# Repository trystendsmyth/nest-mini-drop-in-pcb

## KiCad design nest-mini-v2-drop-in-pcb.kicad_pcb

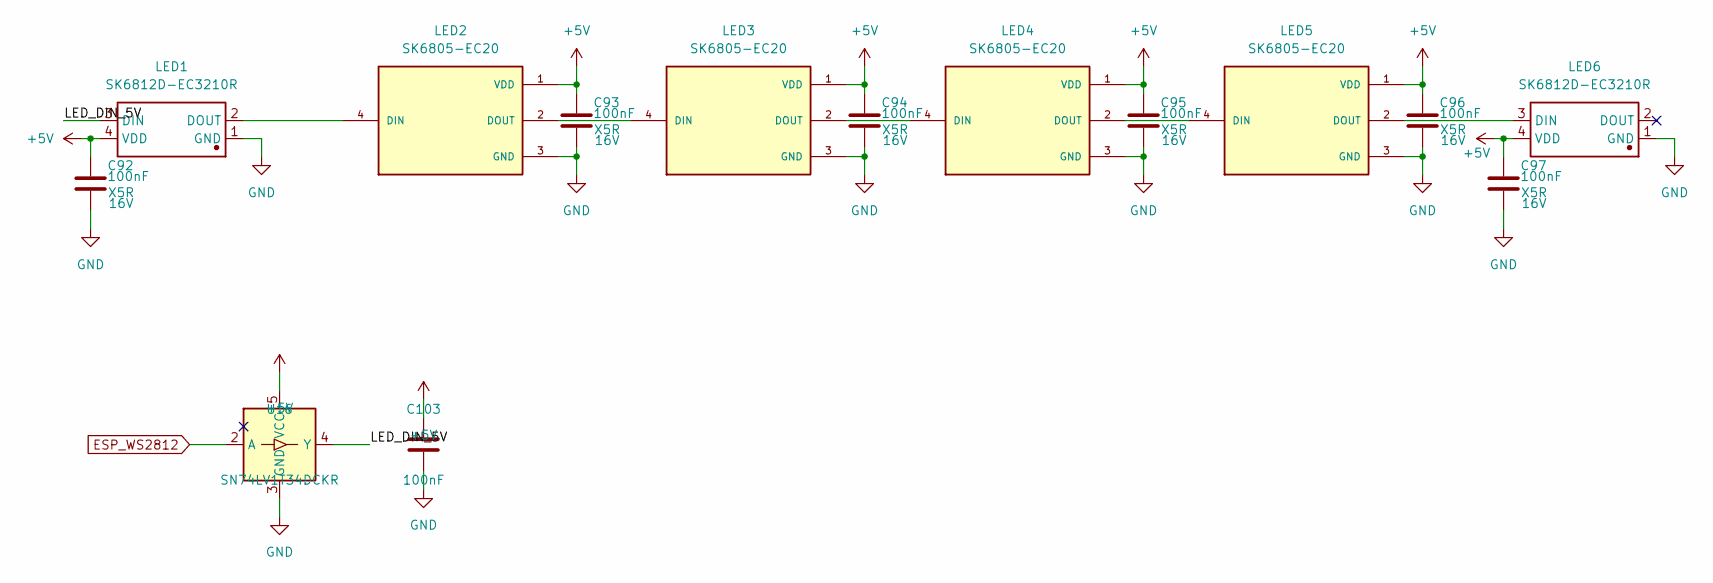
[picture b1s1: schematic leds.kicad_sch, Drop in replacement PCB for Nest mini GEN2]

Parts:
C92, C93, C94, C95, C96, C97: 100nF; C_0402_1005Metric; Voltage 16V; LCSC Part # C1525
C103: 100nF; C_0402_1005Metric; Manufacturer Part CL05B104KO5NNNC; LCSC Part # C1525
LED1, LED6: SK6812D-EC3210R; LED-SMD_4P_SK6812D-EC3210R; Manufacturer Part SK6812D-EC3210R; LCSC Part # C2890041
LED2, LED3, LED4, LED5: SK6805-EC20; Manufacturer Part SK6805-EC20; LCSC Part # C2890036
U16: SN74LV1T34DCKR; SOT-353_SC-70-5; MPN SN74LV1T34DCKR; LCSC Part # C78541

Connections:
+5V: C92.1, C93.1, C94.1, C95.1, C96.1, C97.1, C103.1, LED1.4 (VDD), LED2.1 (VDD), LED3.1 (VDD), LED4.1 (VDD), LED5.1 (VDD), LED6.4 (VDD), U16.5 (VCC); also elsewhere on the board
/LEDs/LED_DIN_5V: LED1.3 (DIN), U16.4 (Y)
ESP_WS2812: U16.2 (A); also elsewhere on the board
GND: C92.2, C93.2, C94.2, C95.2, C96.2, C97.2, C103.2, LED1.1 (GND), LED2.3 (GND), LED3.3 (GND), LED4.3 (GND), LED5.3 (GND), LED6.1 (GND), U16.3 (GND); also elsewhere on the board
unnamed: LED1.2 (DOUT), LED2.4 (DIN)
unnamed: LED2.2 (DOUT), LED3.4 (DIN)
unnamed: LED3.2 (DOUT), LED4.4 (DIN)
unnamed: LED4.2 (DOUT), LED5.4 (DIN)
unnamed: LED5.2 (DOUT), LED6.3 (DIN)

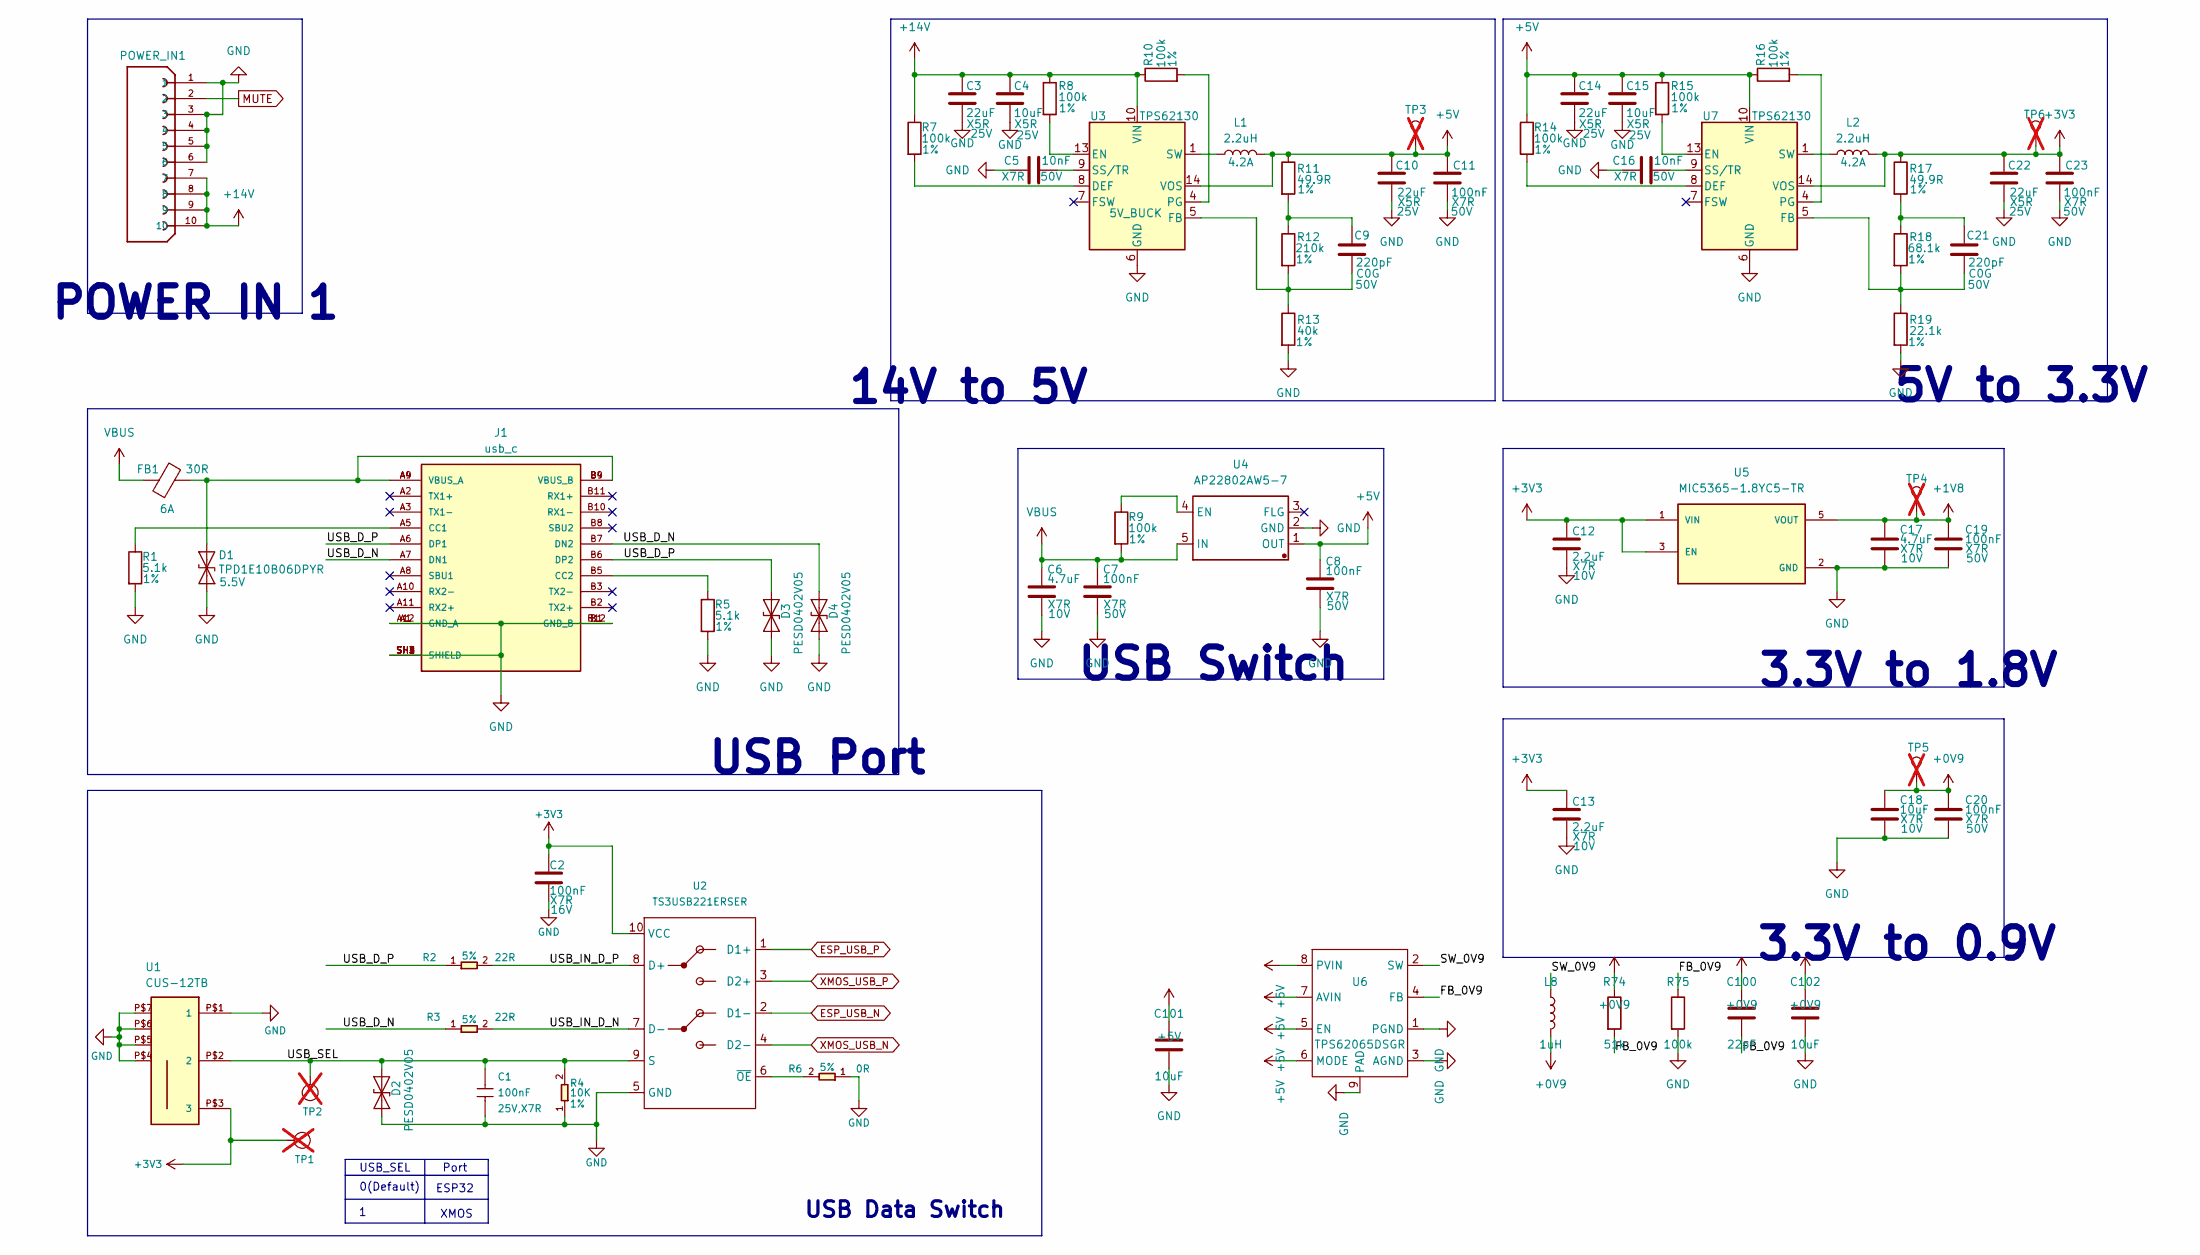
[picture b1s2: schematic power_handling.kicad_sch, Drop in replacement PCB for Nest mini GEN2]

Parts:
C1: 100nF; C_0402_1005Metric; Voltage Rating 25V,X7R; MPN CC0402KRX7R8BB104
C2: 100nF; C_0402_1005Metric; Voltage 16V; Manufacturer Part CL05B104KO5NNNC; LCSC Part # C1525
C3, C10, C14, C22: 22uF; C_0805_2012Metric; Voltage 25V; Manufacturer Part CL21A226MAQNNNE; LCSC Part # C45783
C4, C15: 10uF; C_0805_2012Metric; Voltage 25V; Manufacturer Part CL21A106KAYNNNE; LCSC Part # C15850
C5, C16: 10nF; C_0402_1005Metric; Voltage 50V; Manufacturer Part CL05B103KB5NNNC; LCSC Part # C15195
C6, C17: 4.7uF; C_0603_1608Metric; Voltage 10V; Manufacturer Part GRM188Z71A475KE15D; LCSC Part # C913474
C7, C8: 100nF; C_0603_1608Metric; Voltage 50V; Manufacturer Part CC0603KRX7R9BB104; LCSC Part # C14663
C9, C21: 220pF; C_0603_1608Metric; Voltage 50V; Manufacturer Part 0603CG221J500NT; LCSC Part # C156398
C11, C19, C20, C23: 100nF; C_0805_2012Metric; Voltage 50V; Manufacturer Part CC0805KRX7R9BB104; LCSC Part # C49678
C12, C13: 2.2uF; C_0603_1608Metric; Voltage 10V; Manufacturer Part GRM188R71A225KE15D; LCSC Part # C86018
C18, C101, C102: 10uF; C_0603_1608Metric; Voltage 10V; Manufacturer Part CL10A106KP8NNNC; LCSC Part # C19702
C100: 22pF; C_0402_1005Metric; Manufacturer Part CC0402JRNPO9BN220; LCSC Part # C106203
D1: TPD1E10B06DPYR; TPD1E05U06DPYR; Voltage 5.5V; Manufacturer Part TPD1E10B06DPYR; LCSC Part # C48260
D2, D4: PESD0402V05; D_0402_1005Metric; Manufacturer Part PESD0402V05; LCSC Part # C19626254
D3: PESD0402V05; D_0402_1005Metric; Part C19626254; LCSC Part # C19626254
FB1: 30R; R_0603_1608Metric; Part number BLM18PG300SN1D; LCSC Part # C17305
J1: usb_c; USB-C-SMD_TYPE-C-USB-18; Manufacturer Part 1054500101; LCSC Part # C134092
L1, L2: 2.2uH; L_Cenker_CKCS4020; Manufacturer Part SRP4020TA-2R2M; LCSC Part # C719179
L8: 1uH; L_Murata_DFE201610P; Manufacturer Part DFE201610E-1R0M=P2; LCSC Part # C161082
POWER_IN1: FH34SRJ-10S-0.5SH_50_; HRS_FH34SRJ-10S-0.5SH_50_; Manufacturer Part FH34SRJ-10S-0.5SH(50); LCSC Part # C324723
R1, R5: 5.1k; R_0402_1005Metric; Tolerance 1%; Manufacturer Part 0402WGF5101TCE; LCSC Part # C25905
R2, R3: 22R; R_0402_1005Metric; Tolerance 5%; MPN RC0402JR-0722RL
R4: 10K; R_0402_1005Metric; Tolerance 1%; MPN RC0402FR-0710KL
R6: 0R; R_0402_1005Metric; Tolerance 5%; MPN RC0402JR-070RL
R7, R8, R9, R10, R14, R15, R16: 100k; R_0402_1005Metric; Tolerance 1%; Manufacturer Part 0402WGJ0104TCE; LCSC Part # C25530
R11, R17: 49.9R; R_0603_1608Metric; Tolerance 1%; Manufacturer Part 0603WAF499JT5E; LCSC Part # C23185
R12: 210k; R_0603_1608Metric; Tolerance 1%; Manufacturer Part 0603WAF2103T5E; LCSC Part # C22952
R13: 40k; R_0603_1608Metric; Tolerance 1%; Manufacturer Part SCR0603F40K; LCSC Part # C3016445
R18: 68.1k; R_0603_1608Metric; Tolerance 1%; Manufacturer Part 0603WAF6812T5E; LCSC Part # C25976
R19: 22.1k; R_0603_1608Metric; Tolerance 1%; Manufacturer Part 0603WAF2212T5E; LCSC Part # C25961
R74: 51k; R_0402_1005Metric; Manufacturer Part RC0402FR-0751KL; LCSC Part # C107229
R75: 100k; R_0402_1005Metric; Manufacturer Part RC0402FR-07100KL; LCSC Part # C60491
TP1: Test Point; TestPoint_Pad_D1.0mm; not fitted
TP2: Test Point; TestPoint_Pad_D1.0mm; Part Type Test Point; not fitted
TP3, TP4, TP5, TP6: TestPoint; TestPoint_Pad_D1.0mm; not fitted
U1: CUS-12TB; CUS-12B
U2: TS3USB221ERSER; MPN TS3USB221ERSER; LCSC Part # C129313
U3, U7: TPS62130; VQFN-16-1EP_3x3mm_P0.5mm_EP1.68x1.68mm_ThermalVias; Manufacturer Part TPS62130ARGTR; LCSC Part # C337502
U4: AP22802AW5-7; SOT-23-5; Manufacturer Part AP22802AW5-7; LCSC Part # C211404
U5: MIC5365-1.8YC5-TR; SOT65P210X110-5N; PARTREV 3.1 - July 16, 2013; LCSC Part # C626087
U6: TPS62065DSGR; Texas_DSG0008A_WSON-8-1EP_2x2mm_P0.5mm_EP0.9x1.6mm; MPN TPS62065DSGR; LCSC Part # C398352

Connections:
+0V9: C18.1, C20.1, C100.1, C102.1, L8.2, R74.1, TP5.1; also elsewhere on the board
+1V8: C17.1, C19.1, TP4.1, U5.5 (VOUT); also elsewhere on the board
+3V3: C2.1, C12.1, C13.1, C22.1, C23.1, L2.2, R17.1, TP1.1 (T), TP6.1, U1.P$3 (3), U2.10 (VCC), U5.1 (VIN), U5.3 (EN), U7.14 (VOS); also elsewhere on the board
+5V: C8.1, C10.1, C11.1, C14.1, C15.1, C101.1, L1.2, R11.1, R14.1, R15.1, R16.1, TP3.1, U3.14 (VOS), U4.1 (OUT), U6.5 (EN), U6.6 (MODE), U6.7 (AVIN), U6.8 (PVIN), U7.10 (VIN), U7.11 (VIN), U7.12 (VIN); also elsewhere on the board
+14V: C3.1, C4.1, POWER_IN1.7, POWER_IN1.8, POWER_IN1.9, POWER_IN1.10, R7.1, R8.1, R10.1, U3.10 (VIN), U3.11 (VIN), U3.12 (VIN); also elsewhere on the board
/Power/FB_0V9: C100.2, R74.2, R75.1, U6.4 (FB)
/Power/SW_0V9: L8.1, U6.2 (SW)
/Power/USB_D_N: D4.2 (A2), J1.A7 (DN1), J1.B7 (DN2), R3.1
/Power/USB_D_P: D3.2 (A2), J1.A6 (DP1), J1.B6 (DP2), R2.1
/Power/USB_IN_D_N: R3.2, U2.7 (D-)
/Power/USB_IN_D_P: R2.2, U2.8 (D+)
/Power/USB_SEL: C1.1, D2.2 (A2), R4.2, TP2.1 (T), U1.P$2 (2), U2.9 (S)
ESP_USB_N: U2.2 (D1-); also elsewhere on the board
ESP_USB_P: U2.1 (D1+); also elsewhere on the board
GND: C1.2, C2.2, C3.2, C4.2, C5.1, C6.2, C7.2, C8.2, C10.2, C11.2, C12.2, C13.2, C14.2, C15.2, C16.1, C17.2, C18.2, C19.2, C20.2, C22.2, C23.2, C101.2, C102.2, D1.1 (A1), D2.1 (A1), D3.1 (A1), D4.1 (A1), J1.A1 (GND_A), J1.A12 (GND_A), J1.B1 (GND_B), J1.B12 (GND_B), J1.SH1 (SHIELD), J1.SH2 (SHIELD), J1.SH3 (SHIELD), J1.SH4 (SHIELD), POWER_IN1.1, POWER_IN1.3, POWER_IN1.4, POWER_IN1.5, POWER_IN1.6, R1.2, R4.1, R5.2, R6.1, R13.2, R19.2, R75.2, U1.P$1 (1), U1.P$4, U1.P$5, U1.P$6, U1.P$7, U2.5 (GND), U3.6 (GND), U3.15 (GND), U3.16 (GND), U3.17 (GND), U4.2 (GND), U5.2 (GND), U6.1 (PGND), U6.3 (AGND), U6.9 (PAD), U7.6 (GND), U7.15 (GND), U7.16 (GND), U7.17 (GND); also elsewhere on the board
MUTE: POWER_IN1.2; also elsewhere on the board
unnamed: C9.1, R11.2, R12.1
unnamed: C21.1, R17.2, R18.1
unnamed: D1.2 (A2), FB1.2, J1.A4 (VBUS_A), J1.A9 (VBUS_A), J1.B4 (VBUS_B), J1.B9 (VBUS_B)
unnamed: J1.A5 (CC1), R1.1
unnamed: J1.B5 (CC2), R5.1
unnamed: L1.1, U3.1 (SW), U3.2 (SW), U3.3 (SW)
unnamed: L2.1, U7.1 (SW), U7.2 (SW), U7.3 (SW)
unnamed: R6.2, U2.6 (~OE)
unnamed: R7.2, U3.8 (DEF)
unnamed: R8.2, U3.13 (EN)
unnamed: C9.2, R12.2, R13.1, U3.5 (FB)
unnamed: R10.2, U3.4 (PG)
unnamed: C5.2, U3.9 (SS/TR)
unnamed: R9.1, U4.4 (EN)
unnamed: R14.2, U7.8 (DEF)
unnamed: R15.2, U7.13 (EN)
unnamed: C21.2, R18.2, R19.1, U7.5 (FB)
unnamed: R16.2, U7.4 (PG)
unnamed: C16.2, U7.9 (SS/TR)
VBUS: C6.1, C7.1, FB1.1, R9.2, U4.5 (IN); also elsewhere on the board
XMOS_USB_N: U2.4 (D2-); also elsewhere on the board
XMOS_USB_P: U2.3 (D2+); also elsewhere on the board

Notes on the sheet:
USB Port
POWER IN 1
USB_SEL
14V to 5V
USB Switch
USB Data Switch
3.3V to 1.8V
ESP32
0(Default)
5V to 3.3V
3.3V to 0.9V
Port
XMOS

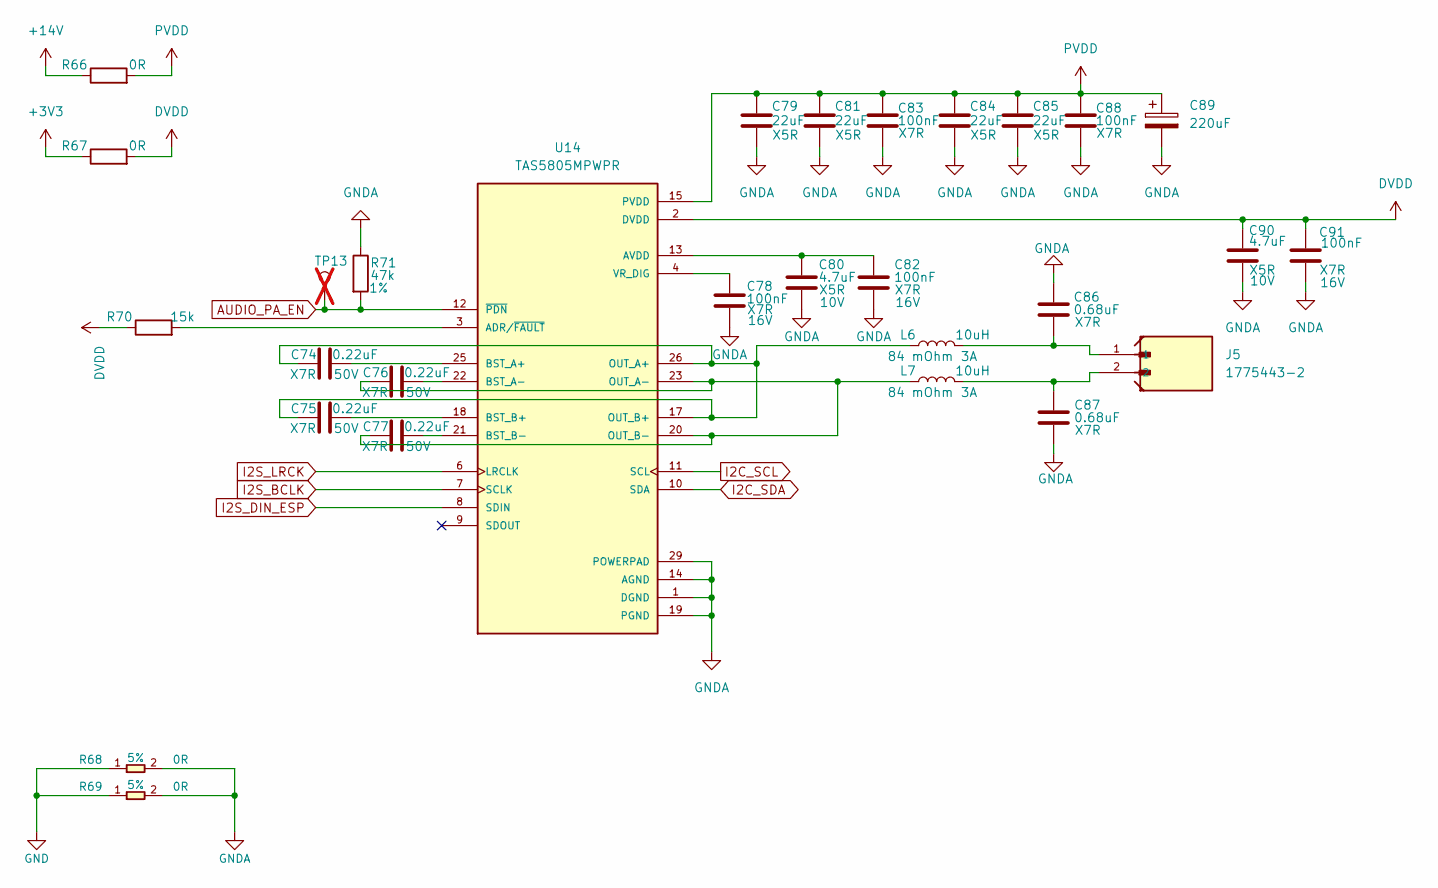
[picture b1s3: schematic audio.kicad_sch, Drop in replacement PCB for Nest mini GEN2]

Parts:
C74, C75, C76, C77: 0.22uF; C_0603_1608Metric; Voltage 50V
C78: 100nF; C_0402_1005Metric; Voltage 16V; Manufacturer Part CL05B104KO5NNNC; LCSC Part # C1525
C79, C81, C84, C85: 22uF; C_0805_2012Metric; Voltage 25V; Manufacturer Part GRM21BR61E226ME44L; LCSC Part # C86816
C80, C90: 4.7uF; C_0603_1608Metric; Voltage 10V
C82, C91: 100nF; C_0603_1608Metric; Voltage 16V
C83, C88: 100nF; C_0402_1005Metric; Voltage 50V; Manufacturer Part CC0402KRX7R9BB104; LCSC Part # C131394
C86, C87: 0.68uF; C_0805_2012Metric; Voltage 100V; Manufacturer Part GRM188R72A10
C89: 220uF; C_Elec_6.3x7.7; Voltage 25V; Manufacturer Part MA25V220M6X8; LCSC Part # C46550464
J5: 1775443-2; PARTREV B5; LCSC Part # C5162845
L6, L7: 10uH; XAL4040-103MEC
R66: 0R; R_1206_3216Metric
R67: 0R; R_0603_1608Metric
R68, R69: 0R; R_0805_2012Metric; Tolerance 5%; MPN 0402WGF0000TCE; LCSC Part # C17168
R70: 15k; R_0402_1005Metric; Manufacturer Part 0402WGF1502TCE; LCSC Part # C25756
R71: 47k; R_0402_1005Metric; Tolerance 1%; Manufacturer Part 0402WGF4702TCE; LCSC Part # C25792
TP13: TestPoint; TestPoint_Pad_D1.0mm; not fitted
U14: TAS5805MPWPR; Manufacturer Part TAS5805MPWPR; LCSC Part # C478472

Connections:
+3V3: R67.1; also elsewhere on the board
+14V: R66.1; also elsewhere on the board
AUDIO_PA_EN: R71.2, TP13.1, U14.12 (~PDN); also elsewhere on the board
DVDD: C90.1, C91.1, R67.2, R70.1, U14.2 (DVDD)
GND: R68.1, R69.1; also elsewhere on the board
GNDA: C78.2, C79.2, C80.2, C81.2, C82.2, C83.2, C84.2, C85.2, C86.2, C87.2, C88.2, C89.2, C90.2, C91.2, R68.2, R69.2, R71.1, U14.1 (DGND), U14.5 (DGND), U14.14 (AGND), U14.19 (PGND), U14.24 (PGND), U14.29 (POWERPAD), U14.30 (POWERPAD), U14.31 (POWERPAD), U14.32 (POWERPAD), U14.33 (POWERPAD), U14.34 (POWERPAD), U14.35 (POWERPAD), U14.36 (POWERPAD), U14.37 (POWERPAD), U14.38 (POWERPAD), U14.39 (POWERPAD), U14.40 (POWERPAD), U14.41 (POWERPAD), U14.42 (POWERPAD), U14.43 (POWERPAD), U14.44 (POWERPAD), U14.45 (POWERPAD), U14.46 (POWERPAD), U14.47 (POWERPAD), U14.48 (POWERPAD), U14.49 (POWERPAD), U14.50 (POWERPAD), U14.51 (POWERPAD), U14.52 (POWERPAD), U14.53 (POWERPAD)
I2C_SCL: U14.11 (SCL); also elsewhere on the board
I2C_SDA: U14.10 (SDA); also elsewhere on the board
I2S_BCLK: U14.7 (SCLK); also elsewhere on the board
I2S_DIN_ESP: U14.8 (SDIN); also elsewhere on the board
I2S_LRCK: U14.6 (LRCLK); also elsewhere on the board
unnamed: C86.1, J5.1, L6.2
unnamed: C87.1, J5.2, L7.2
unnamed: R70.2, U14.3 (ADR/~FAULT)
unnamed: C80.1, C82.1, U14.13 (AVDD)
unnamed: C74.2, U14.25 (BST_A+)
unnamed: C76.2, U14.22 (BST_A-)
unnamed: C75.2, U14.18 (BST_B+)
unnamed: C77.2, U14.21 (BST_B-)
unnamed: C74.1, C75.1, L6.1, U14.17 (OUT_B+), U14.26 (OUT_A+)
unnamed: C76.1, C77.1, L7.1, U14.20 (OUT_B-), U14.23 (OUT_A-)
unnamed: C78.1, U14.4 (VR_DIG)
PVDD: C79.1, C81.1, C83.1, C84.1, C85.1, C88.1, C89.1, R66.2, U14.15 (PVDD), U14.16 (PVDD), U14.27 (PVDD), U14.28 (PVDD)

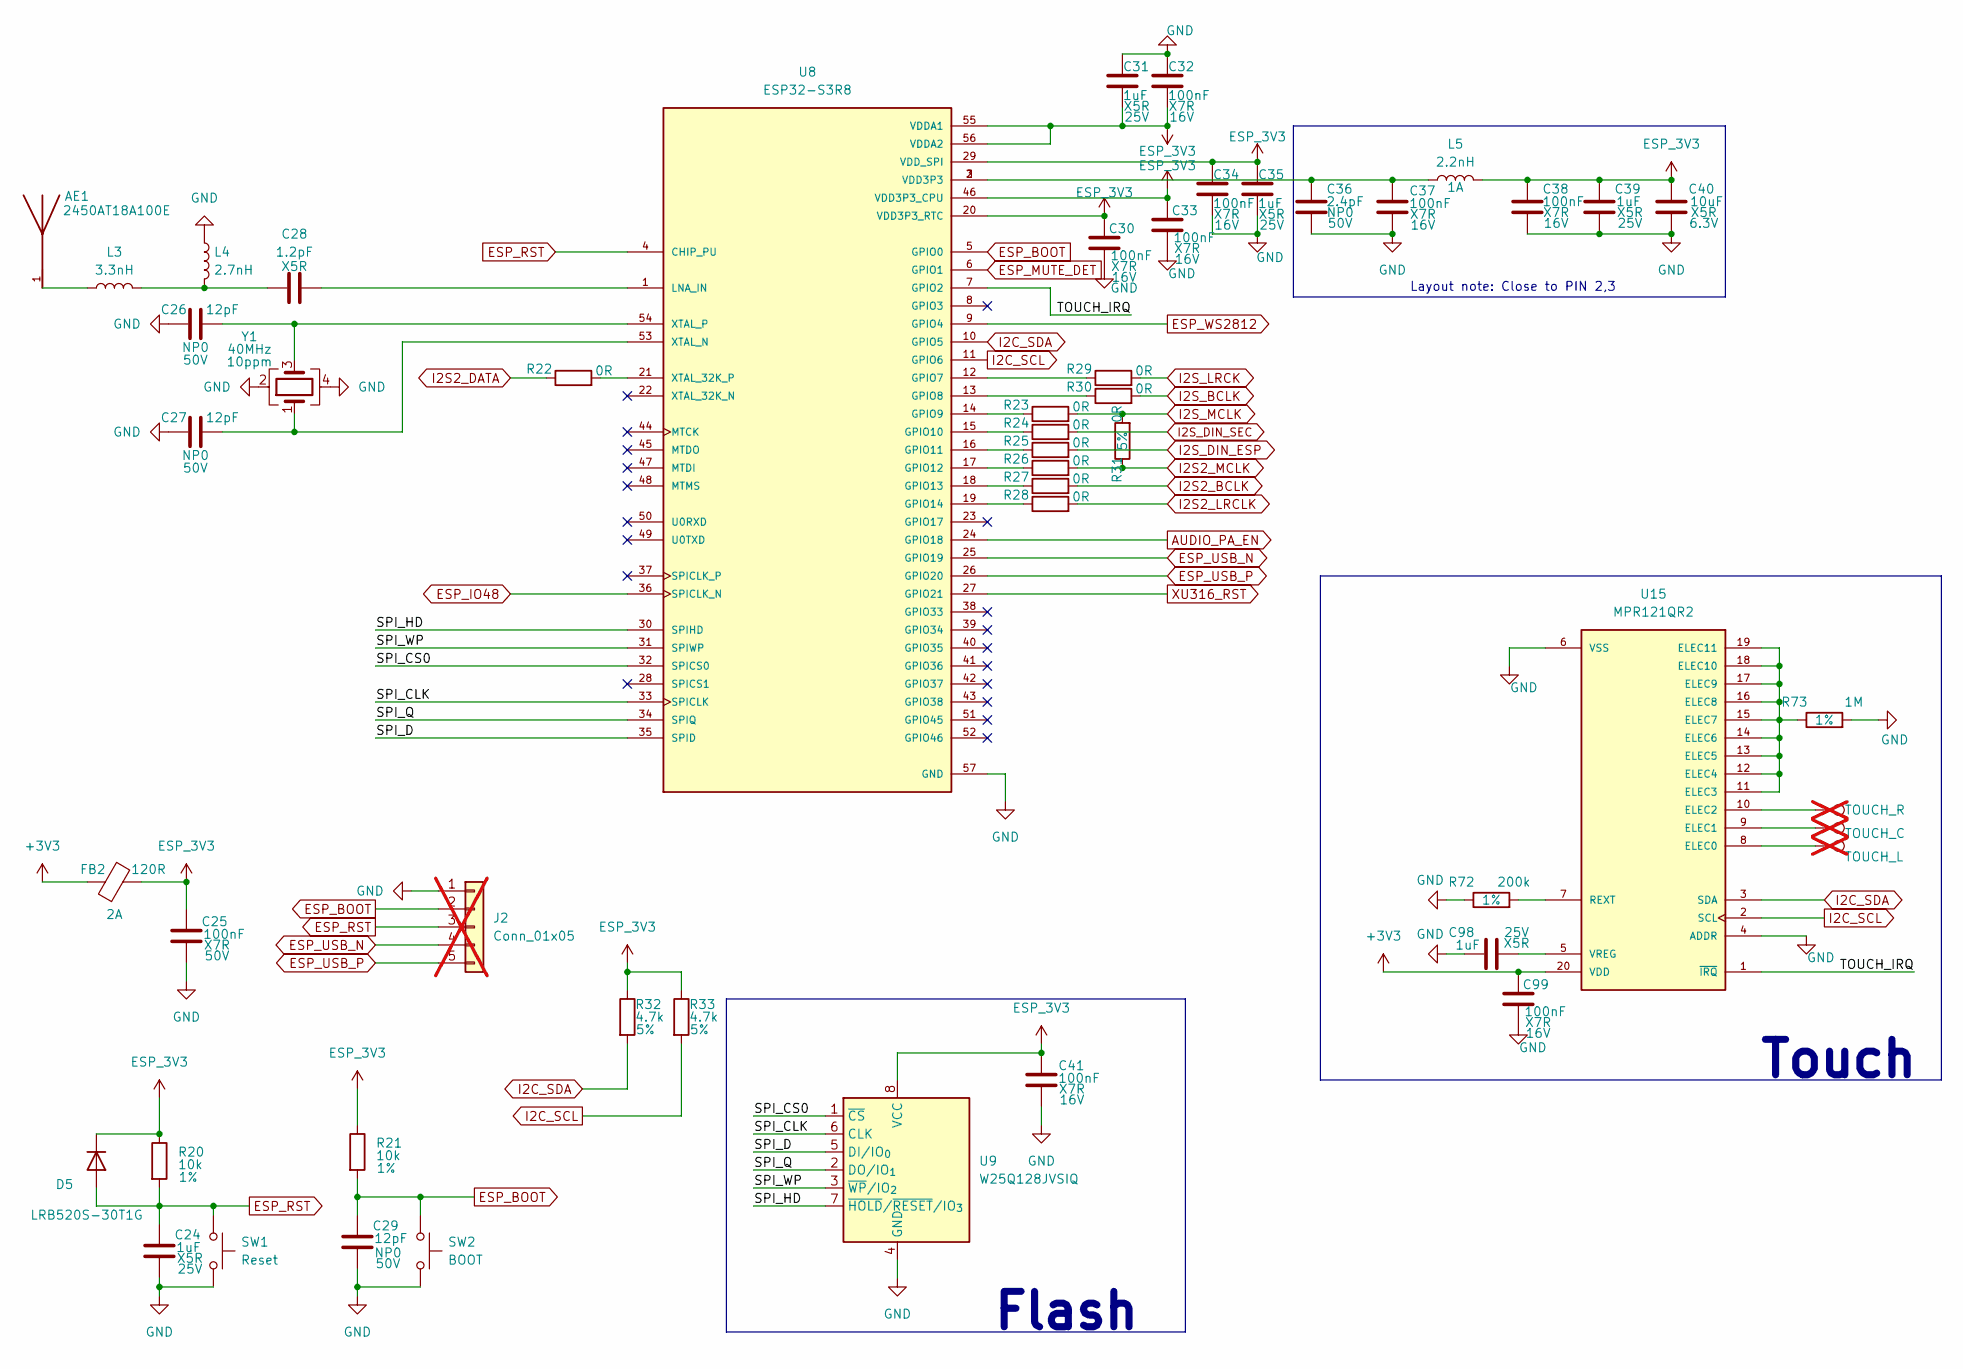
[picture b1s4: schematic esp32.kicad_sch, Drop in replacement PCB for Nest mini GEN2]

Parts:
AE1: 2450AT18A100E; Johanson_2450AT18x100; PARTREV 1.3; LCSC Part # C89334
C24, C31, C35, C39, C98: 1uF; C_0402_1005Metric; Voltage 25V; Manufacturer Part CL05A105KA5NQNC; LCSC Part # C52923
C25: 100nF; C_0603_1608Metric; Voltage 50V; Manufacturer Part CC0603KRX7R9BB104; LCSC Part # C14663
C26, C27, C29: 12pF; C_0402_1005Metric; Voltage 50V; Manufacturer Part 0402CG120J500NT; LCSC Part # C1547
C28: 1.2pF; C_0402_1005Metric; Voltage 10V; Manufacturer Part CC0402BRNPO9BN1R2; LCSC Part # C327292
C30, C32, C33, C34, C37, C38, C41, C99: 100nF; C_0402_1005Metric; Voltage 16V; Manufacturer Part CL05B104KO5NNNC; LCSC Part # C1525
C36: 2.4pF; C_0402_1005Metric; Voltage 50V; Manufacturer Part 0402CG2R4C500NT; LCSC Part # C48346
C40: 10uF; C_0402_1005Metric; Voltage 6.3V; Manufacturer Part CL05A106MQ5NUNC; LCSC Part # C15525
D5: LRB520S-30T1G; D_SOD-523; Manufacturer Part LRB520S-30T1G; LCSC Part # C83680
FB2: 120R; BLM18PG121SN1D; Part number BLM18PG121SN1D; LCSC Part # C14709
J2: Conn_01x05; PinHeader_1x05_P2.54mm_Vertical; not fitted
L3: 3.3nH; L_0402_1005Metric; Manufacturer Part SDCL1005C3N3STDF; LCSC Part # C16526
L4: 2.7nH; L_0402_1005Metric; Manufacturer Part MHQ1005P2N7BT000; LCSC Part # C434826
L5: 2.2nH; L_0402_1005Metric; Manufacturer Part LQG15HS2N2B02D; LCSC Part # C162540
R20, R21: 10k; R_0402_1005Metric; Tolerance 1%; Manufacturer Part 0402WGF1002TCE; LCSC Part # C25744
R22, R23, R24, R25, R26, R27, R28, R29, R30, R31: 0R; R_0402_1005Metric; Tolerance 5%; Manufacturer Part 0402WGF0000TCE; LCSC Part # C17168
R32, R33: 4.7k; R_0402_1005Metric; Tolerance 5%; Manufacturer Part 0402WGF4701TCE; LCSC Part # C25900
R72: 200k; R_0402_1005Metric; Tolerance 1%; MPN 0402WGF2003TCE; LCSC Part # C25764
R73: 1M; R_0402_1005Metric; Tolerance 1%; MPN 0402WGJ0105TCE; LCSC Part # C26087
SW1: Reset; SW-SMD_4P-L4.2-W3.2-P2.15-LS4.5; Manufacturer Part PTS810SJS250SMTRLFS; LCSC Part # C221897
SW2: BOOT; SW-SMD_4P-L4.2-W3.2-P2.15-LS4.5; Manufacturer Part PTS810SJS250SMTRLFS; LCSC Part # C221897
TP14: TOUCH_R; TestPoint_Pad_2.5x2.5mm; not fitted
TP15: TOUCH_C; TestPoint_Pad_2.5x2.5mm; not fitted
TP16: TOUCH_L; TestPoint_Pad_2.5x2.5mm; not fitted
U8: ESP32-S3R8; QFN40P700X700X90-57N; Manufacturer Part ESP32-S3R8; LCSC Part # C2913194
U9: W25Q128JVSIQ; SOIC-8_5.3x5.3mm_P1.27mm; Manufacturer Part W25Q128JVSIQ; LCSC Part # C97521
U15: MPR121QR2; MPN MPR121QR2; LCSC Part # C91322
Y1: 40MHz; Crystal_SMD_2016-4Pin_2.0x1.6mm; Tolerance 10ppm; Manufacturer Part TAXM40M4ZCBCDT2T; LCSC Part # C424431

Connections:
+3V3: C99.1, FB2.1, U15.20 (VDD); also elsewhere on the board
/ESP32-S3R8/SPI_CLK: U8.33 (SPICLK), U9.6 (CLK)
/ESP32-S3R8/SPI_CS0: U8.32 (SPICS0), U9.1 (~CS)
/ESP32-S3R8/SPI_D: U8.35 (SPID), U9.5 (DI/IO_{0})
/ESP32-S3R8/SPI_HD: U8.30 (SPIHD), U9.7 (~HOLD/~RESET/IO_{3})
/ESP32-S3R8/SPI_Q: U8.34 (SPIQ), U9.2 (DO/IO_{1})
/ESP32-S3R8/SPI_WP: U8.31 (SPIWP), U9.3 (~WP/IO_{2})
/ESP32-S3R8/TOUCH_IRQ: U8.7 (GPIO2), U15.1 (~IRQ)
AUDIO_PA_EN: U8.24 (GPIO18); also elsewhere on the board
ESP_3V3: C25.1, C30.1, C31.2, C32.2, C33.1, C34.1, C35.1, C38.1, C39.1, C40.1, C41.1, D5.1 (K), FB2.2, L5.2, R20.1, R21.1, R32.1, R33.1, U8.20 (VDD3P3_RTC), U8.29 (VDD_SPI), U8.46 (VDD3P3_CPU), U8.55 (VDDA1), U8.56 (VDDA2), U9.8 (VCC); also elsewhere on the board
ESP_BOOT: C29.1, J2.2, R21.2, SW2.1, U8.5 (GPIO0)
ESP_IO48: U8.36 (SPICLK_N)
ESP_MUTE_DET: U8.6 (GPIO1); also elsewhere on the board
ESP_RST: C24.1, D5.2 (A), J2.3, R20.2, SW1.1, U8.4 (CHIP_PU)
ESP_USB_N: J2.4, U8.25 (GPIO19); also elsewhere on the board
ESP_USB_P: J2.5, U8.26 (GPIO20); also elsewhere on the board
ESP_WS2812: U8.9 (GPIO4); also elsewhere on the board
GND: C24.2, C25.2, C26.1, C27.1, C29.2, C30.2, C31.1, C32.1, C33.2, C34.2, C35.2, C36.2, C37.2, C38.2, C39.2, C40.2, C41.2, C98.1, C99.2, J2.1, L4.1, R72.1, R73.2, SW1.2, SW2.2, U8.57 (GND), U9.4 (GND), U15.4 (ADDR), U15.6 (VSS), Y1.2, Y1.4; also elsewhere on the board
I2C_SCL: R33.2, U8.11 (GPIO6), U15.2 (SCL); also elsewhere on the board
I2C_SDA: R32.2, U8.10 (GPIO5), U15.3 (SDA); also elsewhere on the board
I2S2_BCLK: R27.2; also elsewhere on the board
I2S2_DATA: R22.1; also elsewhere on the board
I2S2_LRCLK: R28.2; also elsewhere on the board
I2S2_MCLK: R26.2, R31.1; also elsewhere on the board
I2S_BCLK: R30.2; also elsewhere on the board
I2S_DIN_ESP: R25.2; also elsewhere on the board
I2S_DIN_SEC: R24.2; also elsewhere on the board
I2S_LRCK: R29.2; also elsewhere on the board
I2S_MCLK: R23.2, R31.2
unnamed: AE1.1, L3.1
unnamed: C28.1, L3.2, L4.2
unnamed: C36.1, C37.1, L5.1, U8.2 (VDD3P3), U8.3 (VDD3P3)
unnamed: R29.1, U8.12 (GPIO7)
unnamed: R30.1, U8.13 (GPIO8)
unnamed: R23.1, U8.14 (GPIO9)
unnamed: R24.1, U8.15 (GPIO10)
unnamed: R25.1, U8.16 (GPIO11)
unnamed: R26.1, U8.17 (GPIO12)
unnamed: R27.1, U8.18 (GPIO13)
unnamed: R28.1, U8.19 (GPIO14)
unnamed: C28.2, U8.1 (LNA_IN)
unnamed: R22.2, U8.21 (XTAL_32K_P)
unnamed: C27.2, U8.53 (XTAL_N), Y1.1
unnamed: C26.2, U8.54 (XTAL_P), Y1.3
unnamed: TP16.1, U15.8 (ELEC0)
unnamed: TP15.1, U15.9 (ELEC1)
unnamed: TP14.1, U15.10 (ELEC2)
unnamed: R73.1, U15.11 (ELEC3), U15.12 (ELEC4), U15.13 (ELEC5), U15.14 (ELEC6), U15.15 (ELEC7), U15.16 (ELEC8), U15.17 (ELEC9), U15.18 (ELEC10), U15.19 (ELEC11)
unnamed: R72.2, U15.7 (REXT)
unnamed: C98.2, U15.5 (VREG)
XU316_RST: U8.27 (GPIO21); also elsewhere on the board

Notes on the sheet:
Touch
Layout note: Close to PIN 2,3
Flash

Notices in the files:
nest-mini-v2-drop-in-pcb.kicad_pcb:
CERN-OHL-S-2.0
